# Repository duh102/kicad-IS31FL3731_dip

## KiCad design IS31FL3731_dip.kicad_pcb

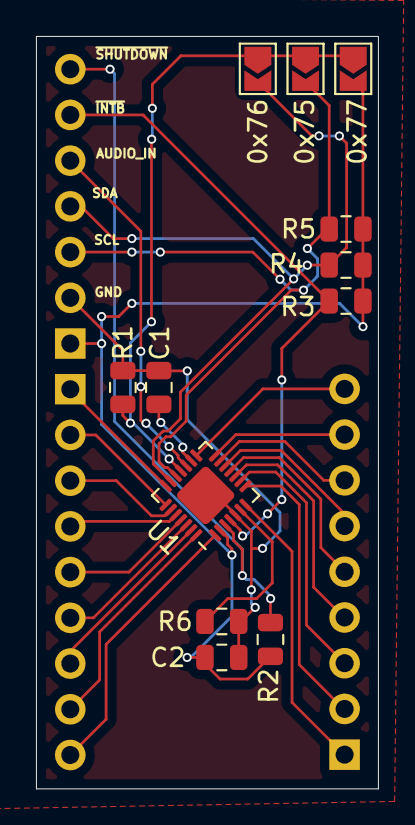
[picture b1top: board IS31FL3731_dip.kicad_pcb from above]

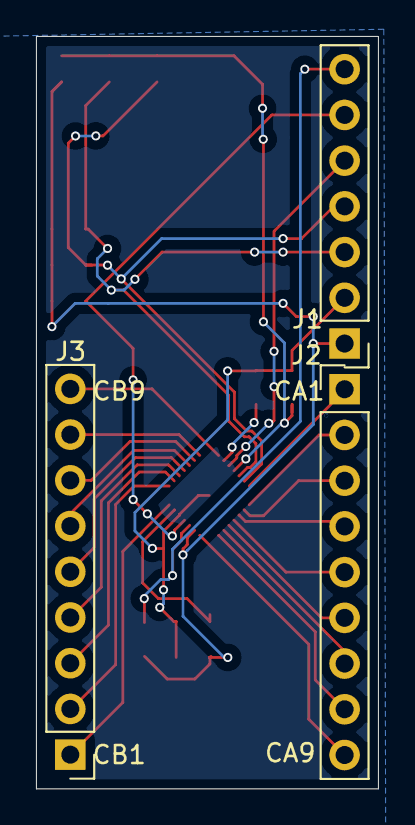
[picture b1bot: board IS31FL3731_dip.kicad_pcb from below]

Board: 2 copper layers, 19.0 x 41.8 mm, 15 parts (3 on the bottom side), 28 nets.

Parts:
0x75, 0x76, 0x77: SolderJumper_2_Open; SolderJumper-2_P1.3mm_Open_TrianglePad1.0x1.5mm
C1: 0.1uF; C_0805_2012Metric
C2: 10.0uF; C_0805_2012Metric
J1: Conn_01x07; PinHeader_1x07_P2.54mm_Vertical
J2, J3: Conn_01x09; PinHeader_1x09_P2.54mm_Vertical
R1, R2, R3, R4, R5, R6: 20kR; R_0805_2012Metric
U1: IS31FL3731; QFN-28-1EP_4x4mm_P0.4mm_EP2.4x2.4mm

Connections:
+5V: 0x77.2, C2.1, J1.1, R2.1, R3.1, R4.1, R5.1, U1.2
/AUDIO_IN: J1.5, U1.17
/SCL: 0x75.2, J1.3, R5.2, U1.19
/SDA: 0x76.2, J1.4, R4.2, U1.20
/~INTB: J1.6, R3.2, U1.4
/~SHUTDOWN: J1.7, R2.2, U1.3
GND: C1.2, C2.2, J1.2, R1.2, R6.2, U1.5, U1.29
unnamed: C1.1, U1.16
unnamed: J2.1, U1.21
unnamed: J2.2, U1.22
unnamed: J2.3, U1.23
unnamed: J2.4, U1.24
unnamed: J2.5, U1.25
unnamed: J2.6, U1.26
unnamed: J2.7, U1.27
unnamed: J2.8, U1.28
unnamed: J2.9, U1.1
unnamed: J3.1, U1.7
unnamed: J3.2, U1.8
unnamed: J3.3, U1.9
unnamed: J3.4, U1.10
unnamed: J3.5, U1.11
unnamed: J3.6, U1.12
unnamed: J3.7, U1.13
unnamed: J3.8, U1.14
unnamed: J3.9, U1.15
unnamed: 0x75.1, 0x76.1, 0x77.1, R1.1, U1.18
unnamed: R6.1, U1.6
